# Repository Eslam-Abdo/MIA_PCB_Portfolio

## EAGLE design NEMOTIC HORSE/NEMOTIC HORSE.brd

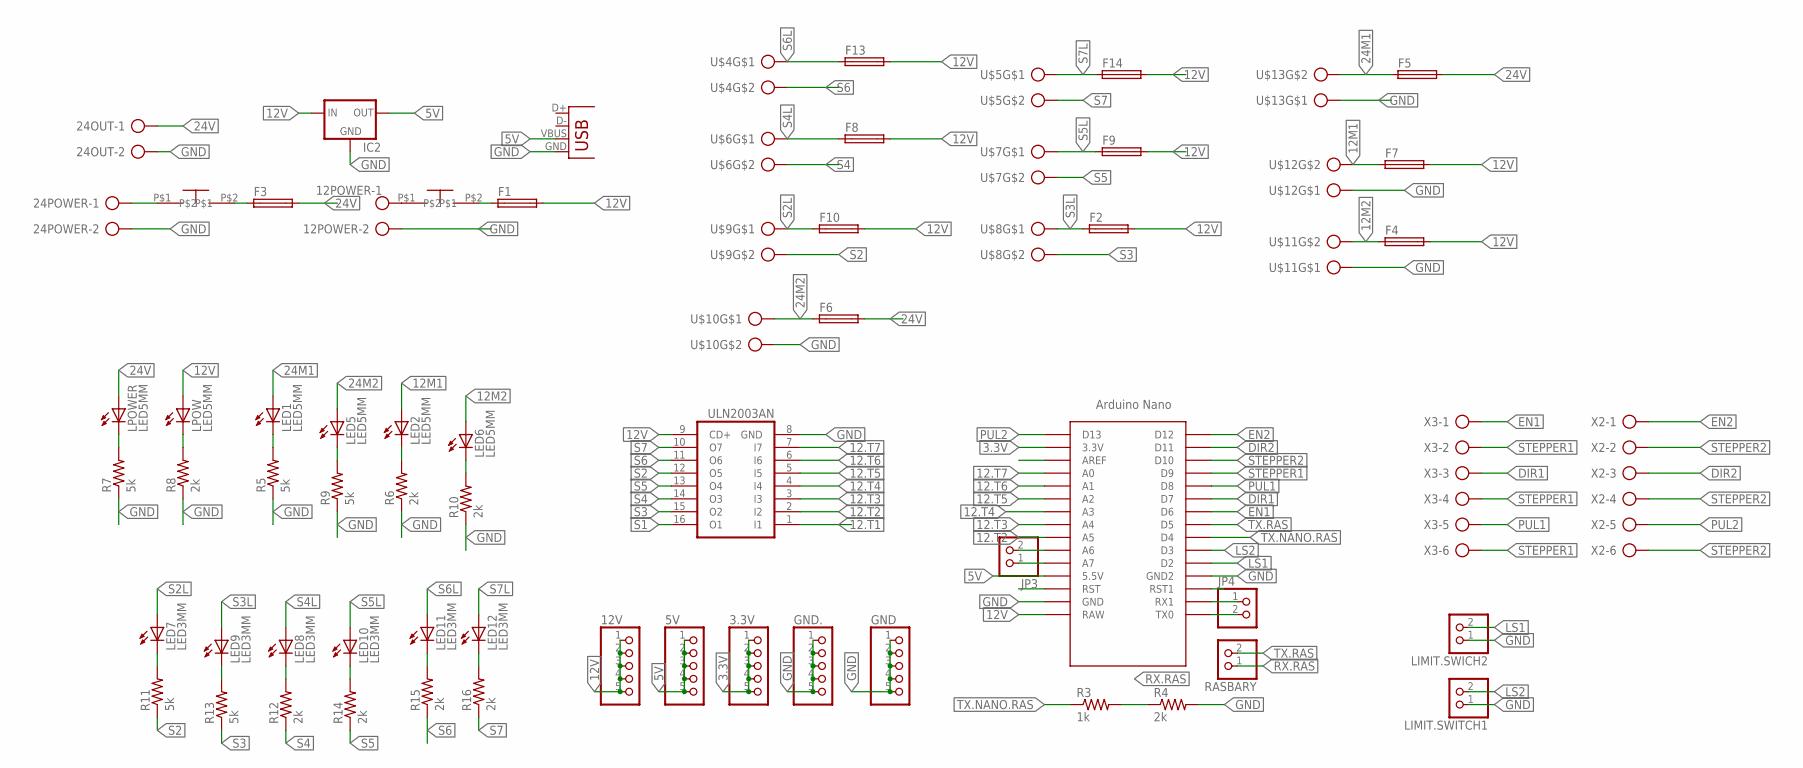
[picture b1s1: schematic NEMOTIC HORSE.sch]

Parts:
3.3V, 5V, 12V: PINHD-1X5; 1X05
12POWER, 24OUT, 24POWER: ROSTA.POWER; W239-302
F1, F2, F3, F4, F5, F6, F7, F8, F9, F10, F13, F14: FUSE_HOLDER; SH22,5A
GND, GND.: PINHD-1X5; 1X05
IC1: ULN2003AN; DIL16
IC2: 78XXS
JP3, JP4: PINHD-1X2; 1X02
LED1, LED2, LED5, LED6: LED5MM
LED7, LED8, LED9, LED10, LED11, LED12: LED3MM
LIMIT.SWICH2, LIMIT.SWITCH1: PINHD-1X2; 1X02
LPOW: LED5MM
LPOWER: LED5MM
R3: 1k; 0204/7
R4, R6, R8, R10: 2k; 0204/7
R5, R7, R9: 5k; 0204/7
R11, R13: 5k; 0204/5
R12, R14, R15, R16: 2k; 0204/5
RASBARY: PINHD-1X2; 1X02
RASBERY.POWER: USB-A-H
U$1: ARDUINO_NANO; NANO
U$2, U$3: SWITCH_2; ON_OFF
U$4, U$5, U$6, U$7, U$8, U$9, U$10, U$11, U$12, U$13: CON_PTR_2; AK300/2
X2, X3: CON_PTR_6; AK300/6

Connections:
3.3V: 3.3V.1, 3.3V.2, 3.3V.3, 3.3V.4, 3.3V.5, U$1.3.3V
5V: 5V.1, 5V.2, 5V.3, 5V.4, 5V.5, IC2.OUT, RASBERY.POWER.VBUS, U$1.5V (5.5V)
12.T1: IC1.1 (I1)
12.T2: IC1.2 (I2), U$1.A5
12.T3: IC1.3 (I3), U$1.A4
12.T4: IC1.4 (I4), U$1.A3
12.T5: IC1.5 (I5), U$1.A2
12.T6: IC1.6 (I6), U$1.A1
12.T7: IC1.7 (I7), U$1.A0
12M1: F7.1, LED2.A, U$12.2
12M2: F4.1, LED6.A, U$11.2
12V: 12V.1, 12V.2, 12V.3, 12V.4, 12V.5, F1.2, F2.2, F4.2, F7.2, F8.2, F9.2, F10.2, F13.2, F14.2, IC1.9 (CD+), IC2.IN, LPOW.A, U$1.RAW
24M1: F5.1, LED1.A, U$13.2
24M2: F6.1, LED5.A, U$10.1
24V: 24OUT.1, F3.2, F5.2, F6.2, LPOWER.A
DIR1: U$1.D7, X3.3
DIR2: U$1.D11, X2.3
EN1: U$1.D6, X3.1
EN2: U$1.D12, X2.1
GND: 12POWER.2, 24OUT.2, 24POWER.2, GND.1, GND.2, GND.3, GND.4, GND.5, GND..1, GND..2, GND..3, GND..4, GND..5, IC1.8 (GND), IC2.GND, LIMIT.SWICH2.1, LIMIT.SWITCH1.1, R4.2, R5.1, R6.1, R7.1, R8.1, R9.1, R10.1, RASBERY.POWER.GND, U$1.GND, U$1.GND1 (GND2), U$10.2, U$11.1, U$12.1, U$13.1
LS1: LIMIT.SWICH2.2, U$1.D2
LS2: LIMIT.SWITCH1.2, U$1.D3
unnamed: 24POWER.1, U$2.P$1
unnamed: LED1.K (C), R5.2
unnamed: F3.1, U$2.P$2
unnamed: LED2.K (C), R6.2
unnamed: LED5.K (C), R9.2
unnamed: LED6.K (C), R10.2
unnamed: LED7.K (C), R11.2
unnamed: LPOWER.K (C), R7.2
unnamed: LPOW.K (C), R8.2
unnamed: LED8.K (C), R12.2
unnamed: JP4.1, U$1.RX1
unnamed: JP4.2, U$1.TX0
unnamed: LED9.K (C), R13.2
unnamed: LED10.K (C), R14.2
unnamed: LED11.K (C), R15.2
unnamed: LED12.K (C), R16.2
unnamed: JP3.1, U$1.A7
unnamed: JP3.2, U$1.A6
unnamed: 12POWER.1, U$3.P$1
unnamed: F1.1, U$3.P$2
PUL1: U$1.D8, X3.5
PUL2: U$1.D13, X2.5
RX.RAS: R3.2, R4.1, RASBARY.1
S1: IC1.16 (O1)
S2: IC1.12 (O5), R11.1, U$9.2
S2L: F10.1, LED7.A, U$9.1
S3: IC1.15 (O2), R13.1, U$8.2
S3L: F2.1, LED9.A, U$8.1
S4: IC1.14 (O3), R12.1, U$6.2
S4L: F8.1, LED8.A, U$6.1
S5: IC1.13 (O4), R14.1, U$7.2
S5L: F9.1, LED10.A, U$7.1
S6: IC1.11 (O6), R15.1, U$4.2
S6L: F13.1, LED11.A, U$4.1
S7: IC1.10 (O7), R16.1, U$5.2
S7L: F14.1, LED12.A, U$5.1
STEPPER1: U$1.D9, X3.2, X3.4, X3.6
STEPPER2: U$1.D10, X2.2, X2.4, X2.6
TX.NANO.RAS: R3.1, U$1.D4
TX.RAS: RASBARY.2, U$1.D5

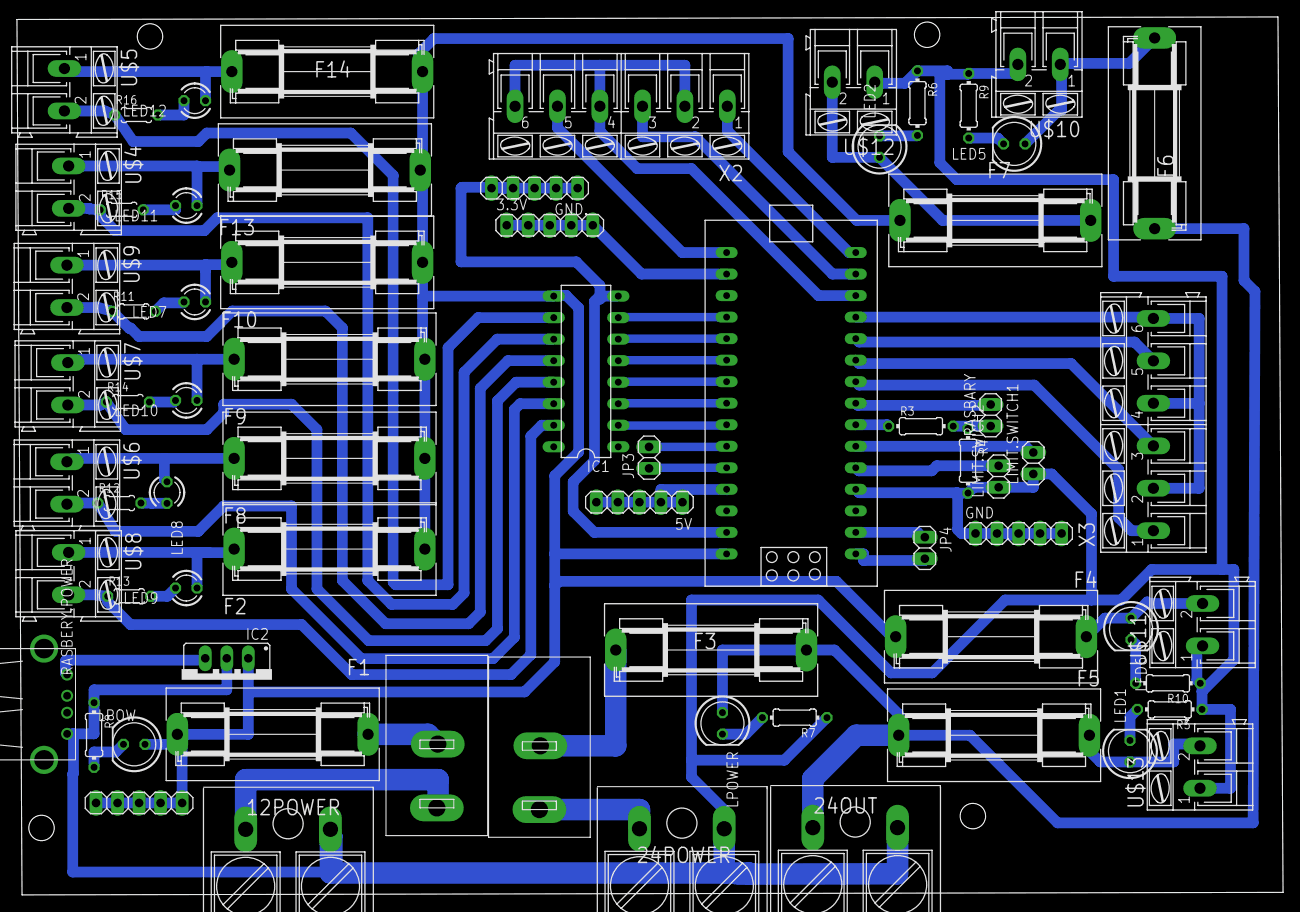
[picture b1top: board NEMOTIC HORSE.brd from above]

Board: 2 copper layers, 149.4 x 103.6 mm, 69 parts (0 on the bottom side), 60 nets.

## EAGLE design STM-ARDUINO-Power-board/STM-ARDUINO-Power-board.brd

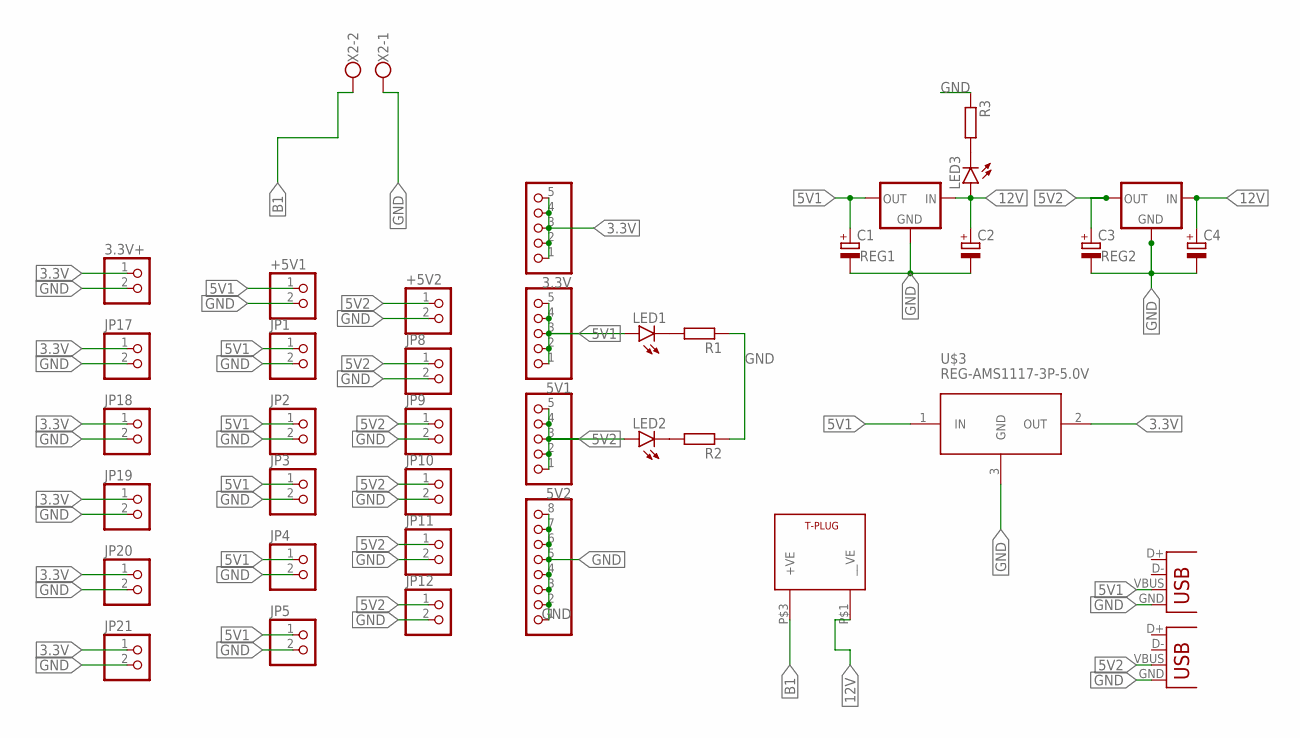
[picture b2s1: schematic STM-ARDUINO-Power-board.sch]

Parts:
3.3V, 5V1, 5V2: PINHD-1X5; 1X05
3.3V+: PINHD-2_DATA; 1X02_DATA
+5V1, +5V2: PINHD-2_DATA; 1X02_DATA
C1, C2, C3, C4: CAP_POL; E3,5-8
GND: PINHD-1X8; 1X08
JP1, JP2, JP3, JP4, JP5, JP8, JP9, JP10, JP11, JP12, JP17, JP18, JP19, JP20, JP21: PINHD-2_DATA; 1X02_DATA
LED1, LED2, LED3: LED5MM
R1, R2, R3: R-EU_0204/7; 0204/7
REG1, REG2: 78XX-METAL; TO3-79
U$3: REG-AMS1117-3P-5.0V; REG-AMS1117-3P
U$5: T_CONNECTOR; T-PLUG
USB1, USB2: USB-A-H
X2: ROSTA.POWER; W239-302

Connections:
3.3V: 3.3V.1, 3.3V.2, 3.3V.3, 3.3V.4, 3.3V.5, 3.3V+.1, JP17.1, JP18.1, JP19.1, JP20.1, JP21.1, U$3.2 (OUT)
5V1: 5V1.1, 5V1.2, 5V1.3, 5V1.4, 5V1.5, +5V1.1, C1.+, JP1.1, JP2.1, JP3.1, JP4.1, JP5.1, LED1.A, REG1.1 (OUT), U$3.1 (IN), USB1.VBUS
5V2: 5V2.1, 5V2.2, 5V2.3, 5V2.4, 5V2.5, +5V2.1, C3.+, JP8.1, JP9.1, JP10.1, JP11.1, JP12.1, LED2.A, REG2.1 (OUT), USB2.VBUS
12V: C2.+, C4.+, LED3.A, REG1.3 (IN), REG2.3 (IN), U$5.P$1 (__VE)
B1: U$5.P$3 (+VE), X2.2
GND: 3.3V+.2, +5V1.2, +5V2.2, C1.-, C2.-, C3.-, C4.-, GND.1, GND.2, GND.3, GND.4, GND.5, GND.6, GND.7, GND.8, JP1.2, JP2.2, JP3.2, JP4.2, JP5.2, JP8.2, JP9.2, JP10.2, JP11.2, JP12.2, JP17.2, JP18.2, JP19.2, JP20.2, JP21.2, R1.1, R2.1, R3.1, REG1.2 (GND), REG2.2 (GND), U$3.3 (GND), USB1.GND, USB2.GND, X2.1
unnamed: LED1.K (C), R1.2
unnamed: LED2.K (C), R2.2
unnamed: LED3.K (C), R3.2

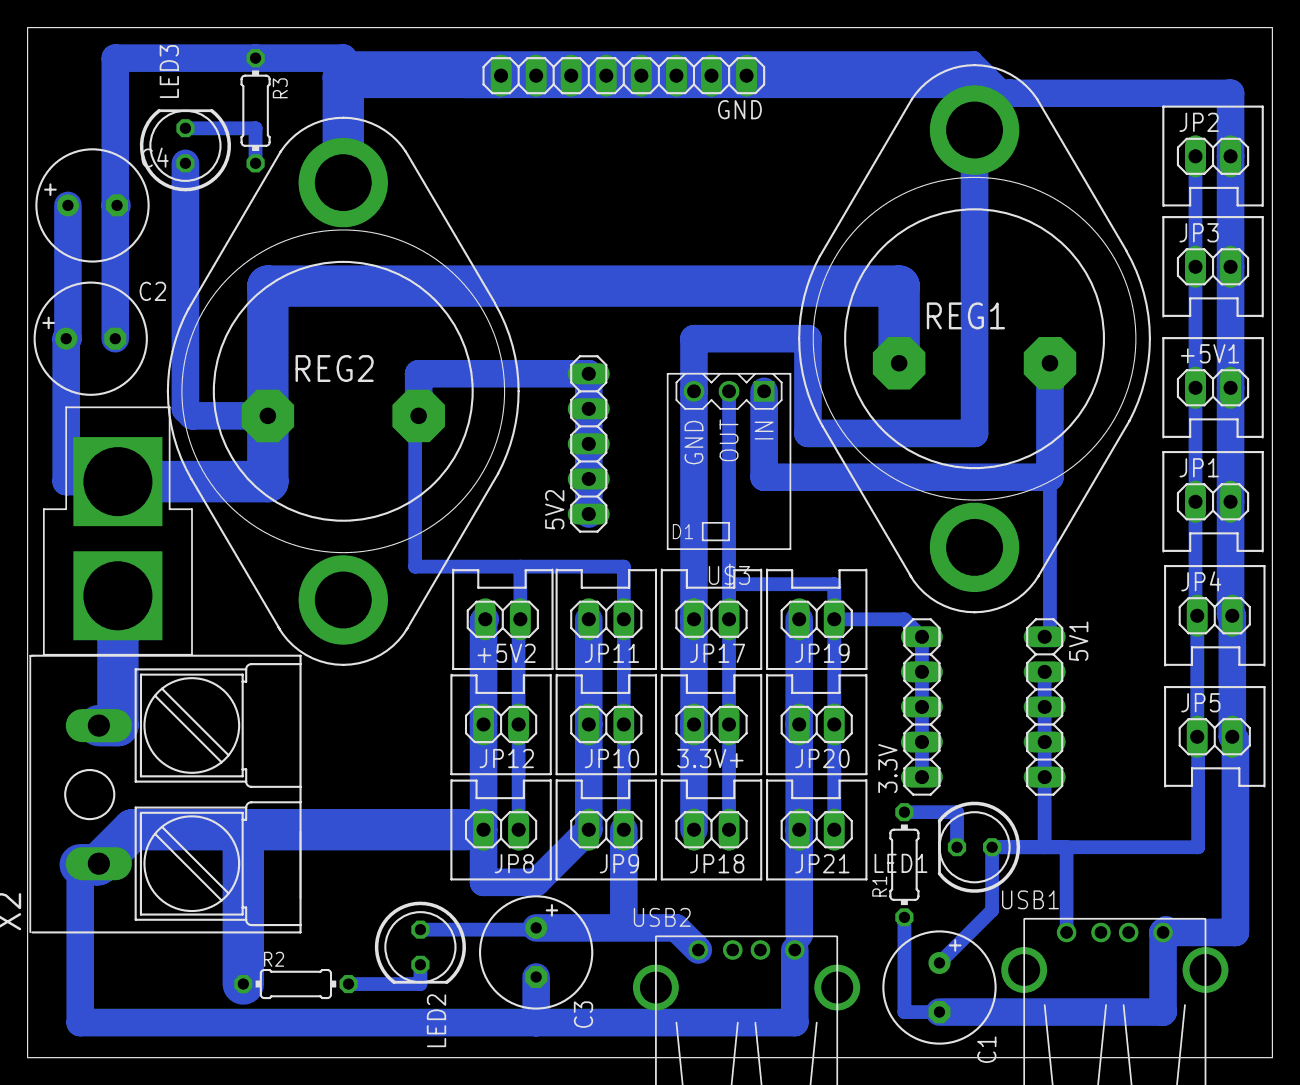
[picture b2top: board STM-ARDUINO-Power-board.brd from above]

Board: 2 copper layers, 90.2 x 74.6 mm, 39 parts (0 on the bottom side), 9 nets.

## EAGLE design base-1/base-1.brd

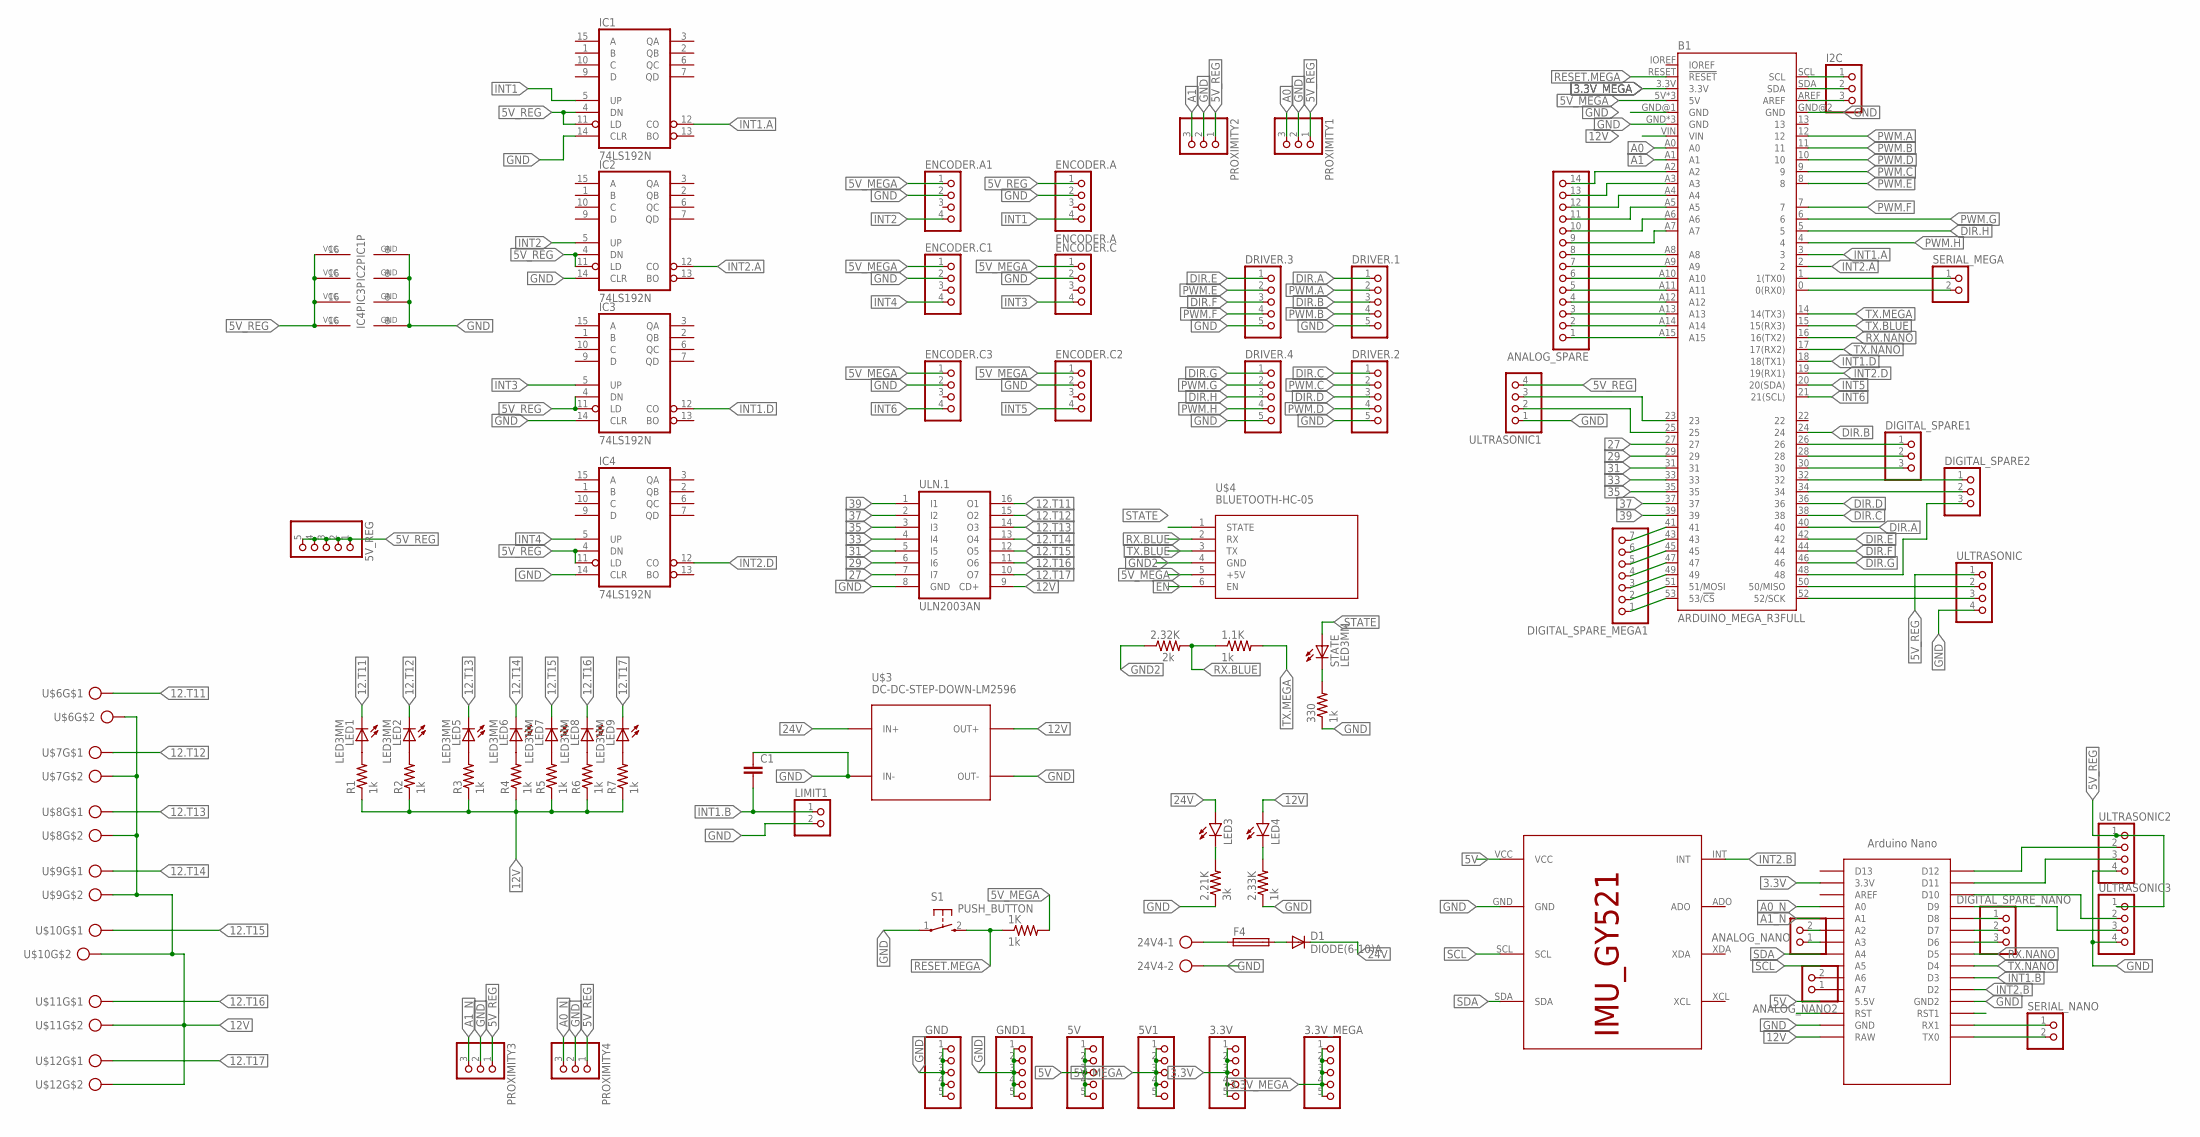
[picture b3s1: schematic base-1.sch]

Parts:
1.1K, 1K, 2.33K, 330: 1k; 0204/5
2.21K: 3k; 0204/5
2.32K: 2k; 0204/5
3.3V, 3.3V_MEGA, 5V, 5V1, 5V_REG: PINHD-1X5; 1X05
24V4: ROSTA.POWER; W239-302
ANALOG_NANO, ANALOG_NANO2: PINHD-1X2; 1X02
ANALOG_SPARE: PINHD-1X14; 1X14
B1: ARDUINO_MEGA_R3FULL; ARDUINO_MEGA_NO_SILK
C1: CAPACITOR; C025-025X050
D1: DIODE(6-10)A; DO201-15
DIGITAL_SPARE1, DIGITAL_SPARE2: PINHD-1X3; 1X03
DIGITAL_SPARE_MEGA1: PINHD-1X7; 1X07
DIGITAL_SPARE_NANO: PINHD-1X3; 1X03
DRIVER.1, DRIVER.2, DRIVER.3, DRIVER.4: PINHD-1X5; 1X05
ENCODER.A: ENCODER.A; 1X04
ENCODER.A1, ENCODER.C, ENCODER.C1, ENCODER.C2, ENCODER.C3: PINHD-1X4; 1X04
F4: FUSE_HOLDER; SH22,5A
GND, GND1: PINHD-1X5; 1X05
I2C: PINHD-1X3; 1X03
IC1, IC2, IC3, IC4: 74LS192N; DIL16
LED1, LED2, LED5, LED6, LED7, LED8, LED9: LED3MM
LED3, LED4: LED5MM
LIMIT1: PINHD-1X2; 1X02
PROXIMITY1, PROXIMITY2, PROXIMITY3, PROXIMITY4: PINHD-1X3; 1X03
R1, R2, R3, R4, R5, R6, R7: 1k; 0204/5
S1: PUSH_BUTTON; B3F-10XX
SERIAL_MEGA: PINHD-1X2; 1X02
SERIAL_NANO: PINHD-1X2; 1X02
STATE: LED3MM
U$1: ARDUINO_NANO; NANO
U$3: DC-DC-STEP-DOWN-LM2596
U$4: BLUETOOTH-HC-05; WIRELESS-BLUETOOTH-HC-05
U$5: IMU_ROBOCON_GY521; IMU_GY521
U$6, U$7, U$8, U$9, U$10, U$11, U$12: CON_PTR_2; AK300/2
ULN.1: ULN2003AN; DIL16
ULTRASONIC, ULTRASONIC1, ULTRASONIC2, ULTRASONIC3: PINHD-1X4; 1X04

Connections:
3.3V: 3.3V.1, 3.3V.2, 3.3V.3, 3.3V.4, 3.3V.5, U$1.3.3V
3.3V_MEGA: 3.3V_MEGA.1, 3.3V_MEGA.2, 3.3V_MEGA.3, 3.3V_MEGA.4, 3.3V_MEGA.5, B1.3.3V
5V: 5V.1, 5V.2, 5V.3, 5V.4, 5V.5, U$1.5V (5.5V), U$5.VCC
5V_MEGA: 1K.2, 5V1.1, 5V1.2, 5V1.3, 5V1.4, 5V1.5, B1.5V, B1.5V@1 (5V), B1.5V@2 (5V), ENCODER.A1.1, ENCODER.C.1, ENCODER.C1.1, ENCODER.C2.1, ENCODER.C3.1, U$4.5 (+5V)
5V_REG: 5V_REG.1, 5V_REG.2, 5V_REG.3, 5V_REG.4, 5V_REG.5, ENCODER.A.1, IC1.4 (DN), IC1.11 (LD), IC1.16 (VCC), IC2.4 (DN), IC2.11 (LD), IC2.16 (VCC), IC3.4 (DN), IC3.11 (LD), IC3.16 (VCC), IC4.4 (DN), IC4.11 (LD), IC4.16 (VCC), PROXIMITY1.1, PROXIMITY2.1, PROXIMITY3.1, PROXIMITY4.1, ULTRASONIC.1, ULTRASONIC1.4, ULTRASONIC2.1, ULTRASONIC3.1
12.T11: LED1.K (C), U$6.1, ULN.1.16 (O1)
12.T12: LED2.K (C), U$7.1, ULN.1.15 (O2)
12.T13: LED5.K (C), U$8.1, ULN.1.14 (O3)
12.T14: LED6.K (C), U$9.1, ULN.1.13 (O4)
12.T15: LED7.K (C), U$10.1, ULN.1.12 (O5)
12.T16: LED8.K (C), U$11.1, ULN.1.11 (O6)
12.T17: LED9.K (C), U$12.1, ULN.1.10 (O7)
12V: B1.VIN, LED4.A, R1.1, R2.1, R3.1, R4.1, R5.1, R6.1, R7.1, U$1.RAW, U$3.OUT+, U$6.2, U$7.2, U$8.2, U$9.2, U$10.2, U$11.2, U$12.2, ULN.1.9 (CD+)
24V: D1.C, LED3.A, U$3.IN+
27: B1.27, ULN.1.7 (I7)
29: B1.29, ULN.1.6 (I6)
31: B1.31, ULN.1.5 (I5)
33: B1.33, ULN.1.4 (I4)
35: B1.35, ULN.1.3 (I3)
37: B1.37, ULN.1.2 (I2)
39: B1.39, ULN.1.1 (I1)
48: B1.48, DIGITAL_SPARE2.3
A0: B1.A0, PROXIMITY1.3
A0_N: PROXIMITY4.3, U$1.A0
A1: B1.A1, PROXIMITY2.3
A1_N: PROXIMITY3.3, U$1.A1
DIR.A: B1.40, DRIVER.1.1
DIR.B: B1.24, DRIVER.1.3
DIR.C: B1.38, DRIVER.2.1
DIR.D: B1.36, DRIVER.2.3
DIR.E: B1.42, DRIVER.3.1
DIR.F: B1.44, DRIVER.3.3
DIR.G: B1.46, DRIVER.4.1
DIR.H: B1.5, DRIVER.4.3
EN: U$4.6 (EN)
GND: 2.21K.1, 2.33K.1, 24V4.2, 330.1, B1.GND, B1.GND@1 (GND), B1.GND@2 (GND), B1.GND@3 (GND), B1.GND@4 (GND), C1.1, DRIVER.1.5, DRIVER.2.5, DRIVER.3.5, DRIVER.4.5, ENCODER.A.2, ENCODER.A1.2, ENCODER.C.2, ENCODER.C1.2, ENCODER.C2.2, ENCODER.C3.2, GND.1, GND.2, GND.3, GND.4, GND.5, GND1.1, GND1.2, GND1.3, GND1.4, GND1.5, IC1.8 (GND), IC1.14 (CLR), IC2.8 (GND), IC2.14 (CLR), IC3.8 (GND), IC3.14 (CLR), IC4.8 (GND), IC4.14 (CLR), LIMIT1.2, PROXIMITY1.2, PROXIMITY2.2, PROXIMITY3.2, PROXIMITY4.2, S1.1, U$1.GND, U$1.GND1 (GND2), U$3.IN-, U$3.OUT-, U$5.GND, ULN.1.8 (GND), ULTRASONIC.4, ULTRASONIC1.1, ULTRASONIC2.4, ULTRASONIC3.4
GND2: 2.32K.1, U$4.4 (GND)
INT1: ENCODER.A.4, IC1.5 (UP)
INT1.A: B1.3, IC1.12 (CO)
INT1.B: C1.2, LIMIT1.1, U$1.D3
INT1.D: B1.18 (18(TX1)), IC3.12 (CO)
INT2: ENCODER.A1.4, IC2.5 (UP)
INT2.A: B1.2, IC2.12 (CO)
INT2.B: U$1.D2, U$5.INT
INT2.D: B1.19 (19(RX1)), IC4.12 (CO)
INT3: ENCODER.C.4, IC3.5 (UP)
INT4: ENCODER.C1.4, IC4.5 (UP)
INT5: B1.20 (20(SDA)), ENCODER.C2.4
INT6: B1.21 (21(SCL)), ENCODER.C3.4
unnamed: B1.SCL, I2C.1
unnamed: B1.SDA, I2C.2
unnamed: B1.AREF, I2C.3
unnamed: ANALOG_SPARE.1, B1.A15
unnamed: 24V4.1, F4.1
unnamed: ANALOG_SPARE.2, B1.A14
unnamed: ANALOG_SPARE.3, B1.A13
unnamed: ANALOG_SPARE.4, B1.A12
unnamed: ANALOG_SPARE.5, B1.A11
unnamed: ANALOG_SPARE.6, B1.A10
unnamed: ANALOG_SPARE.7, B1.A9
unnamed: ANALOG_SPARE.8, B1.A8
unnamed: ANALOG_SPARE.9, B1.A7
unnamed: B1.1 (1(TX0)), SERIAL_MEGA.1
unnamed: B1.0 (0(RX0)), SERIAL_MEGA.2
unnamed: 330.2, STATE.K (C)
unnamed: 2.21K.2, LED3.K (C)
unnamed: 2.33K.2, LED4.K (C)
unnamed: D1.A, F4.2
unnamed: LED1.A, R1.2
unnamed: LED2.A, R2.2
unnamed: LED5.A, R3.2
unnamed: LED6.A, R4.2
unnamed: LED7.A, R5.2
unnamed: LED8.A, R6.2
unnamed: LED9.A, R7.2
unnamed: B1.23, ULTRASONIC1.3
unnamed: B1.25, ULTRASONIC1.2
unnamed: ANALOG_NANO.1, U$1.A3
unnamed: ANALOG_NANO.2, U$1.A2
unnamed: B1.50 (50/MISO), ULTRASONIC.2
unnamed: B1.52 (52/SCK), ULTRASONIC.3
unnamed: ANALOG_NANO2.1, U$1.A7
unnamed: ANALOG_NANO2.2, U$1.A6
unnamed: B1.26, DIGITAL_SPARE1.1
unnamed: ANALOG_SPARE.10, B1.A6
unnamed: ANALOG_SPARE.11, B1.A5
unnamed: ANALOG_SPARE.12, B1.A4
unnamed: B1.28, DIGITAL_SPARE1.2
unnamed: B1.30, DIGITAL_SPARE1.3
unnamed: ANALOG_SPARE.13, B1.A3
unnamed: ANALOG_SPARE.14, B1.A2
unnamed: B1.32, DIGITAL_SPARE2.1
unnamed: B1.34, DIGITAL_SPARE2.2
unnamed: B1.41, DIGITAL_SPARE_MEGA1.7
unnamed: B1.45, DIGITAL_SPARE_MEGA1.5
unnamed: B1.43, DIGITAL_SPARE_MEGA1.6
unnamed: B1.47, DIGITAL_SPARE_MEGA1.4
unnamed: B1.49, DIGITAL_SPARE_MEGA1.3
unnamed: B1.51 (51/MOSI), DIGITAL_SPARE_MEGA1.2
unnamed: B1.53 (53/!CS), DIGITAL_SPARE_MEGA1.1
unnamed: U$1.D12, ULTRASONIC2.2
unnamed: U$1.D11, ULTRASONIC2.3
unnamed: U$1.D10, ULTRASONIC3.2
unnamed: U$1.D9, ULTRASONIC3.3
unnamed: DIGITAL_SPARE_NANO.1, U$1.D8
unnamed: DIGITAL_SPARE_NANO.2, U$1.D7
unnamed: DIGITAL_SPARE_NANO.3, U$1.D6
unnamed: SERIAL_NANO.1, U$1.RX1
unnamed: SERIAL_NANO.2, U$1.TX0
PWM.A: B1.12, DRIVER.1.2
PWM.B: B1.11, DRIVER.1.4
PWM.C: B1.9, DRIVER.2.2
PWM.D: B1.10, DRIVER.2.4
PWM.E: B1.8, DRIVER.3.2
PWM.F: B1.7, DRIVER.3.4
PWM.G: B1.6, DRIVER.4.2
PWM.H: B1.4, DRIVER.4.4
RESET.MEGA: 1K.1, B1.RESET (!RESET), S1.2 (S)
RX.BLUE: 1.1K.1, 2.32K.2, U$4.2 (RX)
RX.NANO: B1.16 (16(TX2)), U$1.D5
SCL: U$1.A5, U$5.SCL
SDA: U$1.A4, U$5.SDA
STATE: STATE.A, U$4.1 (STATE)
TX.BLUE: B1.15 (15(RX3)), U$4.3 (TX)
TX.MEGA: 1.1K.2, B1.14 (14(TX3))
TX.NANO: B1.17 (17(RX2)), U$1.D4

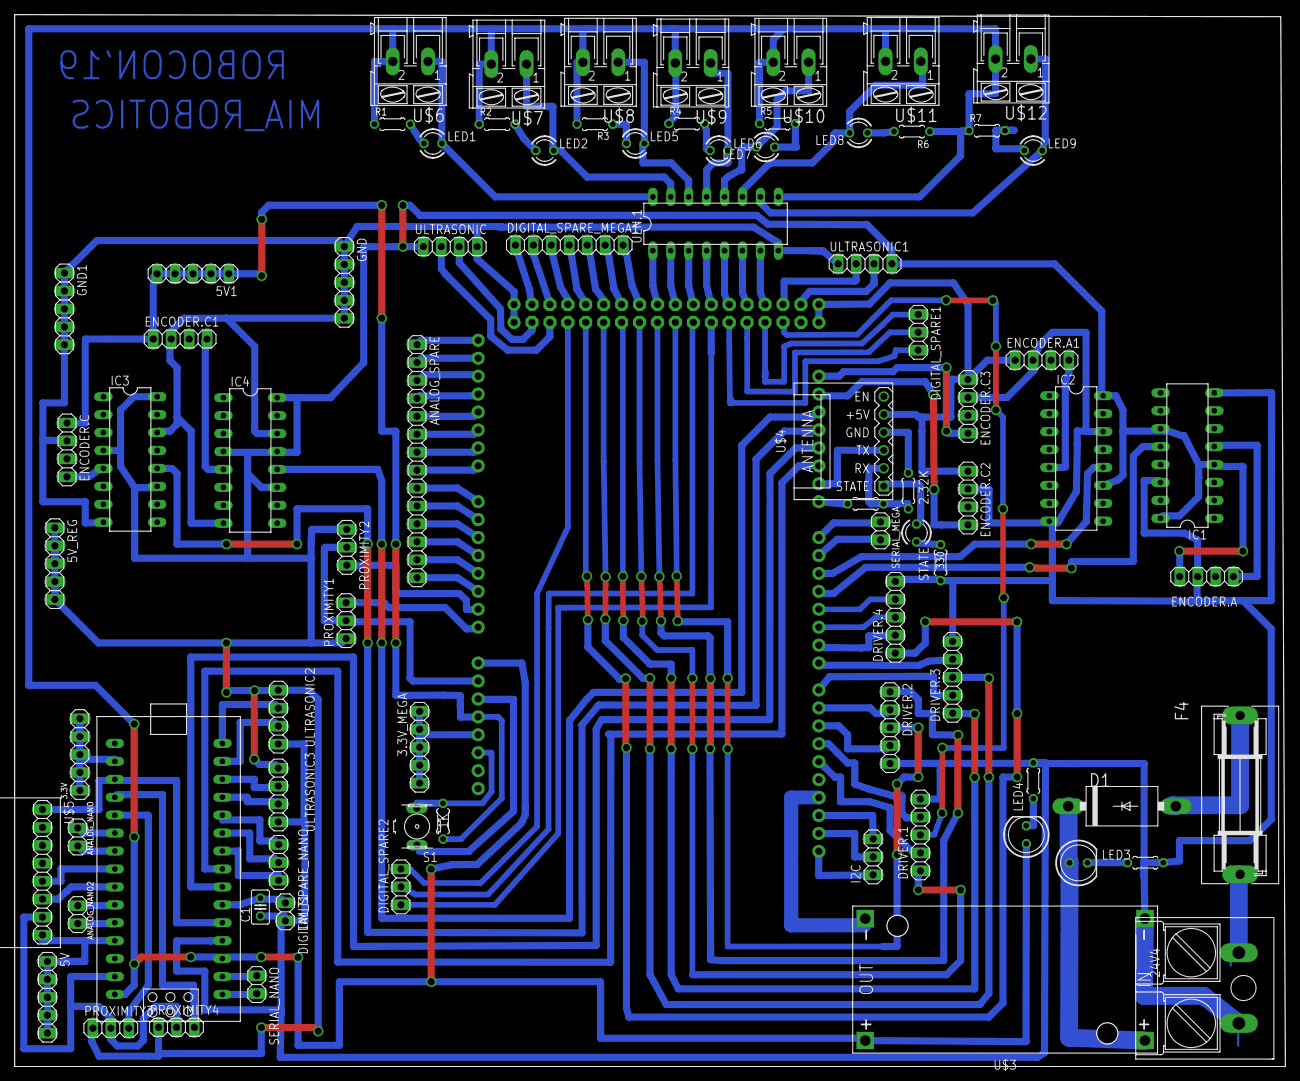
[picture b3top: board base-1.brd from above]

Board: 2 copper layers, 180.0 x 149.0 mm, 81 parts (1 on the bottom side), 125 nets.

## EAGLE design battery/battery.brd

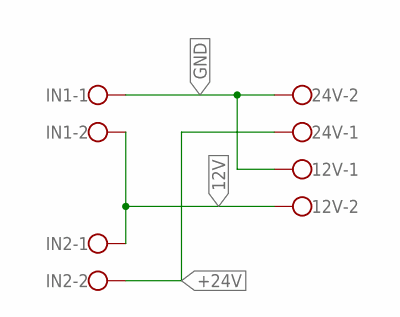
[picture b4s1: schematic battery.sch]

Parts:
12V, 24V: W237-113
IN1, IN2: W237-113

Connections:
12V: 12V.2, IN1.2, IN2.1
+24V: 24V.1, IN2.2
GND: 12V.1, 24V.2, IN1.1

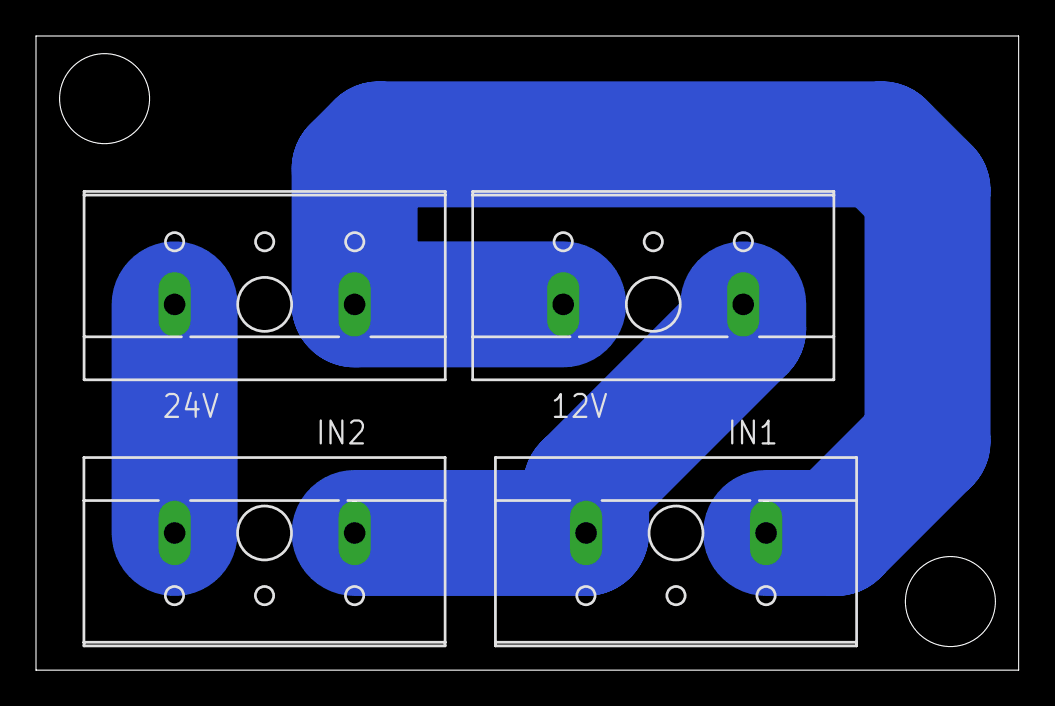
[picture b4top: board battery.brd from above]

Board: 2 copper layers, 54.6 x 35.2 mm, 4 parts (0 on the bottom side), 3 nets.

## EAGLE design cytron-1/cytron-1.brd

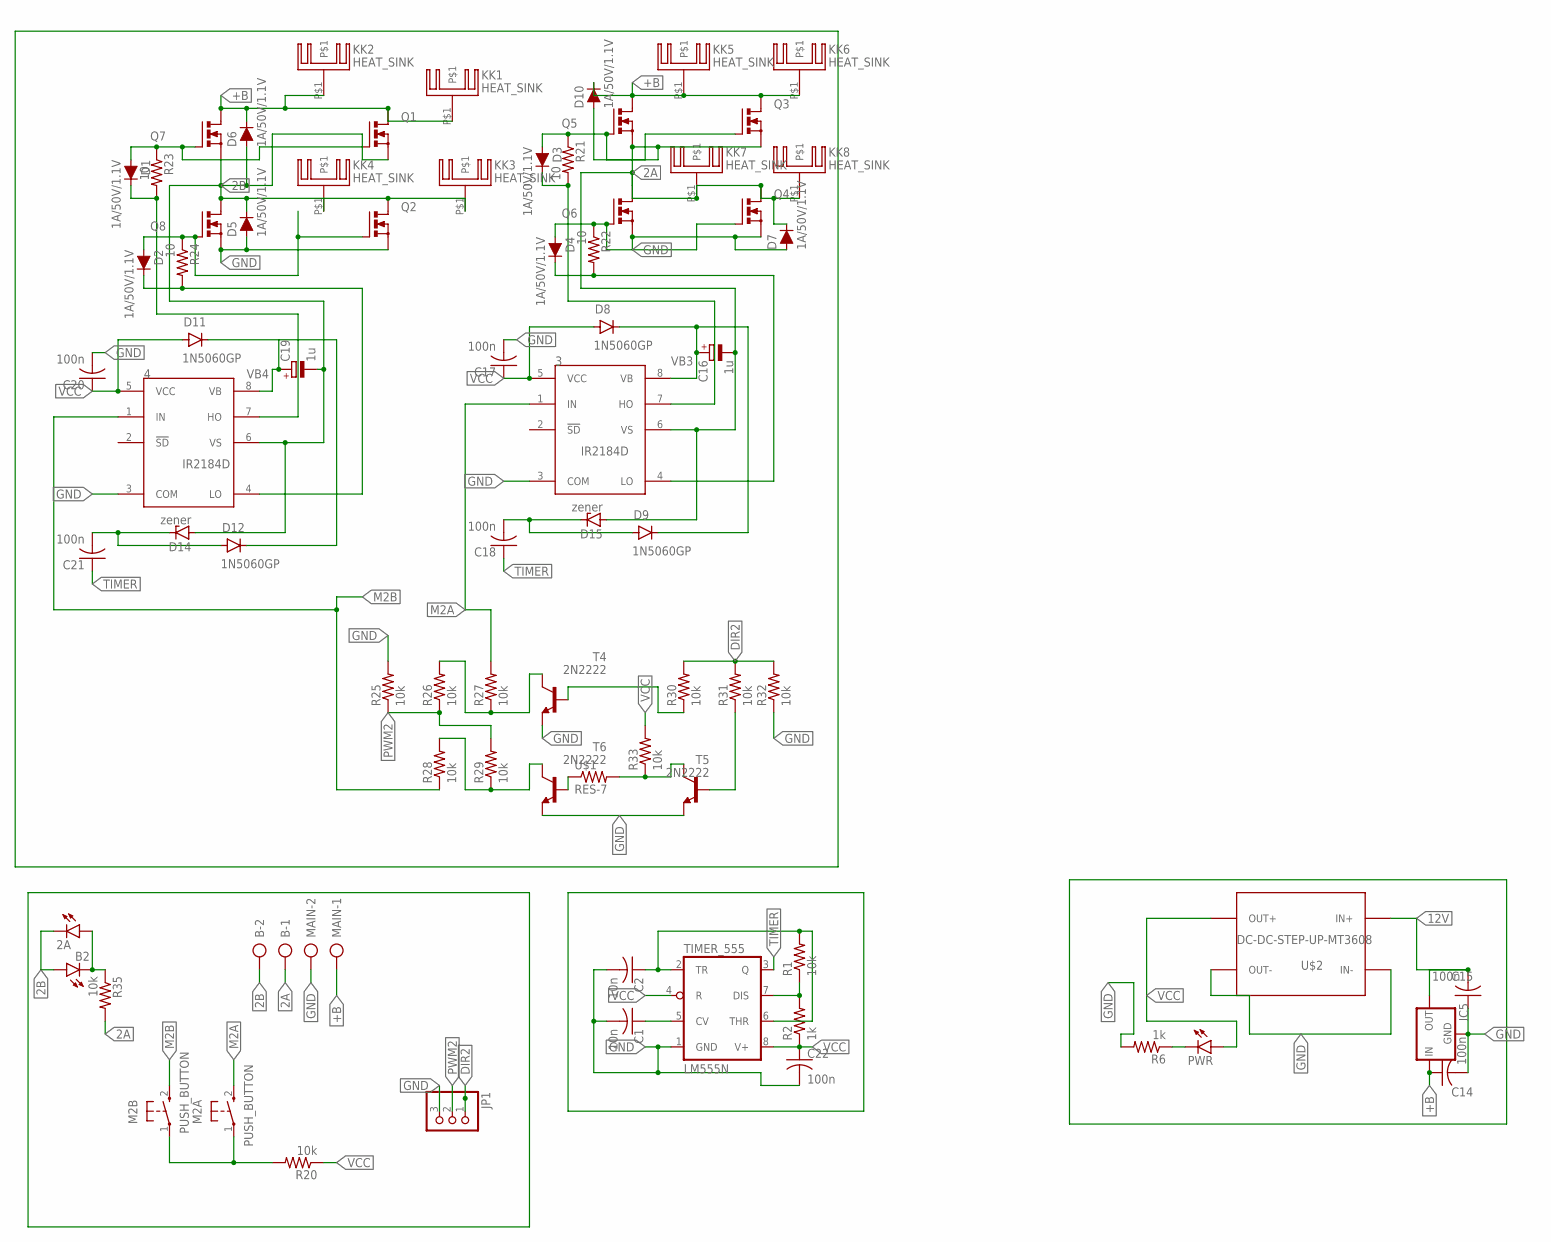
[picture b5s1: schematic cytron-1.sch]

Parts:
2A: LED3MM
3, 4: IR2184D; DIL08
B: ROSTA.POWER; W239-302
B2: LED3MM
C1, C2: 10n; C025-025X050
C14, C15, C17, C18, C20, C21, C22: 100n; C025-025X050
C16, C19: 1u; E5-5
D1, D2, D3, D4, D5, D6, D7, D10: 1A/50V/1.1V; DIODE-1N4001
D8, D9, D11, D12: 1N5060GP; DO15-12
D14, D15: zener; SOD81
IC5: 78XXL
JP1: PINHD-3_DATA; 1X03_DATA
KK1, KK2, KK3, KK4, KK5, KK6, KK7, KK8: HEAT_SINK; SK95-2M3
M2A, M2B: PUSH_BUTTON; B3F-10XX
MAIN: ROSTA.POWER; W239-302
PWR: LED5MM
Q1, Q2, Q3, Q4, Q5, Q6, Q7, Q8: MOSFET_NTO220BV; TO220BV
R1, R20, R25, R26, R27, R28, R29, R30, R31, R32, R33, R35: 10k; 0204/7
R2, R6: 1k; 0204/7
R21, R22, R23, R24: 10; 0204/7
T4, T5, T6: 2N2222; TO18
TIMER_555: LM555N; DIL08
U$1: RES-7; 0204/7
U$2: DC-DC-STEP-UP-MT3608

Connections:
2A: 3.6 (VS), B.1, C16.-, D7.C, D10.A, D15.A, KK7.P$1, KK8.P$1, Q3.S, Q4.D, Q5.S, Q6.D, R35.2
2B: 2A.K (C), 4.6 (VS), B.2, B2.A, C19.-, D5.C, D6.A, D14.A, KK3.P$1, KK4.P$1, Q1.S, Q2.D, Q7.S, Q8.D
12V: C15.2, IC5.OUT, U$2.IN+
+B: C14.1, D6.C, D10.C, IC5.IN, KK1.P$1, KK2.P$1, KK5.P$1, KK6.P$1, MAIN.1, Q1.D, Q3.D, Q5.D, Q7.D
DIR2: JP1.1, R30.2, R31.2, R32.2
GND: 3.3 (COM), 4.3 (COM), C1.2, C2.2, C14.2, C15.1, C17.2, C20.2, C22.2, D5.A, D7.A, IC5.GND, JP1.3, MAIN.2, Q2.S, Q4.S, Q6.S, Q8.S, R6.2, R25.2, R32.1, T4.1 (E), T5.1 (E), T6.1 (E), TIMER_555.1 (GND), U$2.IN-, U$2.OUT-
M2A: 3.1 (IN), M2A.2 (S), R27.2
M2B: 4.1 (IN), M2B.2 (S), R28.1
unnamed: PWR.K (C), R6.1
unnamed: C1.1, TIMER_555.5 (CV)
unnamed: R1.1, R2.2, TIMER_555.7 (DIS)
unnamed: C2.1, R1.2, TIMER_555.2 (TR), TIMER_555.6 (THR)
unnamed: D4.A, Q4.G, Q6.G, R22.1
unnamed: M2A.1, M2B.1, R20.2
unnamed: T6.2 (B), U$1.1
unnamed: D3.A, Q3.G, Q5.G, R21.1
unnamed: 3.4 (LO), D4.C, R22.2
unnamed: 3.7 (HO), D3.C, R21.2
unnamed: C18.2, D9.A, D15.C
unnamed: D2.A, Q2.G, Q8.G, R24.1
unnamed: D1.A, Q1.G, Q7.G, R23.1
unnamed: 4.4 (LO), D2.C, R24.2
unnamed: 4.7 (HO), D1.C, R23.2
unnamed: C21.2, D12.A, D14.C
unnamed: R28.2, R29.1, T6.3 (C)
unnamed: R26.2, R27.1, T4.3 (C)
unnamed: R30.1, T4.2 (B)
unnamed: R33.1, T5.3 (C), U$1.2
unnamed: R31.1, T5.2 (B)
unnamed: 2A.A, B2.K (C), R35.1
PWM2: JP1.2, R25.1, R26.1, R29.2
TIMER: C18.1, C21.1, TIMER_555.3 (Q)
VB3: 3.8 (VB), C16.+, D8.C, D9.C
VB4: 4.8 (VB), C19.+, D11.C, D12.C
VCC: 3.5 (VCC), 4.5 (VCC), C17.1, C20.1, C22.1, D8.A, D11.A, PWR.A, R2.1, R20.1, R33.2, TIMER_555.4 (R), TIMER_555.8 (V+), U$2.OUT+

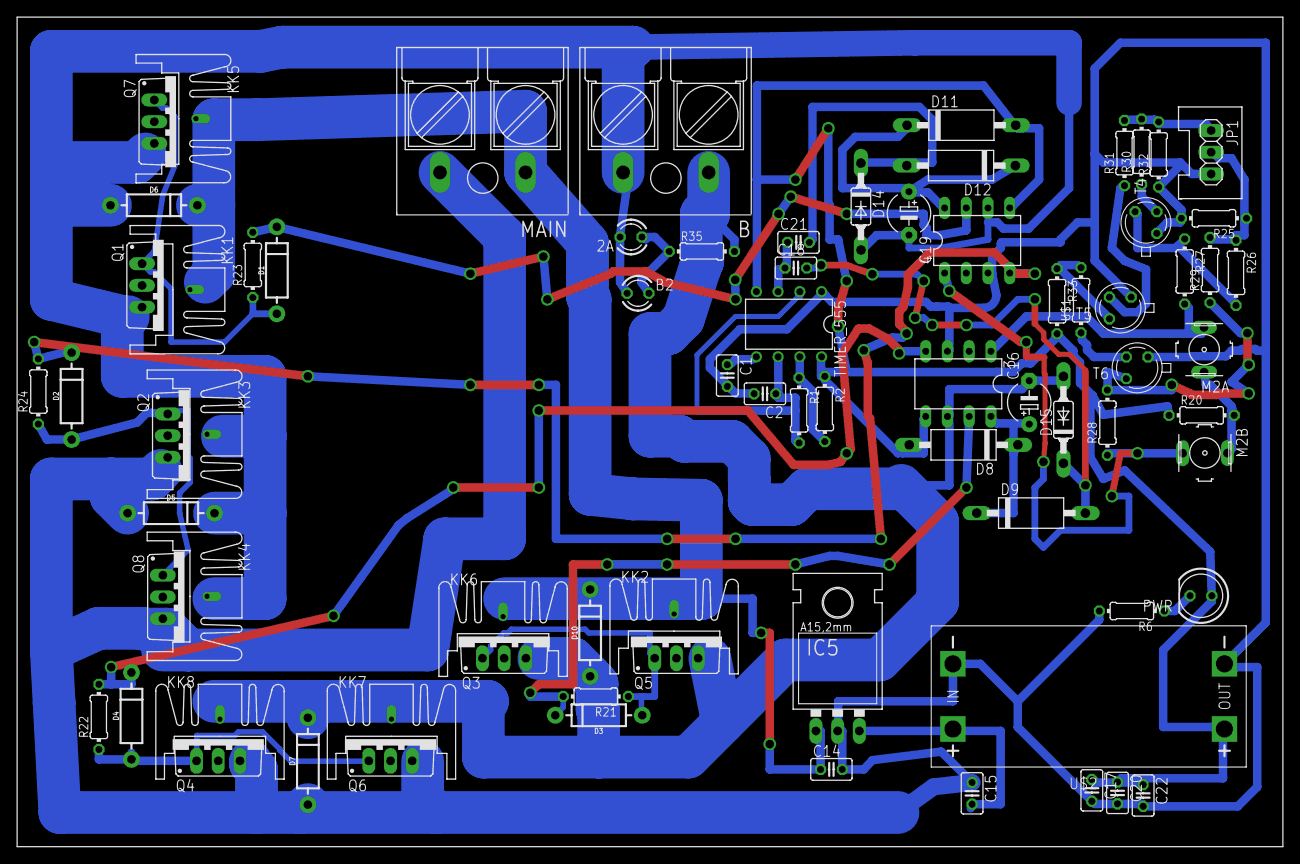
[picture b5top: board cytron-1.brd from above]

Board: 2 copper layers, 148.0 x 97.0 mm, 76 parts (0 on the bottom side), 35 nets.
